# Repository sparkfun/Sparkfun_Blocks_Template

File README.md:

Edison_Mezzanine_Base
=====================

Base Board for Edison Mezzanine stack

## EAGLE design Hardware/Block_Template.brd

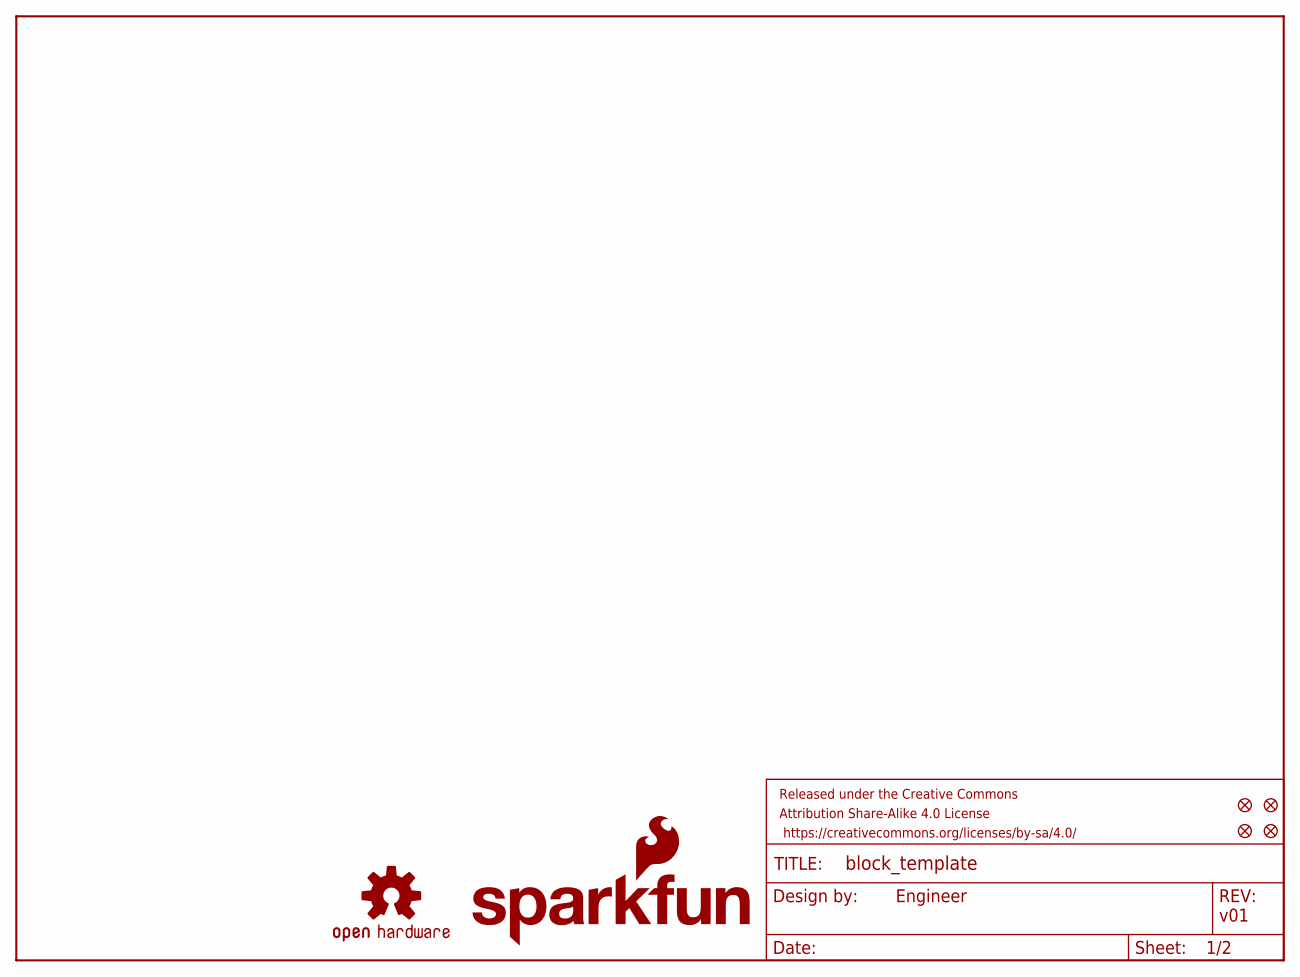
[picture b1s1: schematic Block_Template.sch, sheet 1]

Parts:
FID1, FID2, FID3, FID4: FIDUCIAL1X2; FIDUCIAL-1X2
FRAME1: FRAME-LETTER; CREATIVE_COMMONS
LOGO1: OSHW-LOGOS; OSHW-LOGO-S
LOGO4: SFE_LOGO_NAME_FLAME.1_INCH; SFE_LOGO_NAME_FLAME_.1

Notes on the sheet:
v01
Engineer

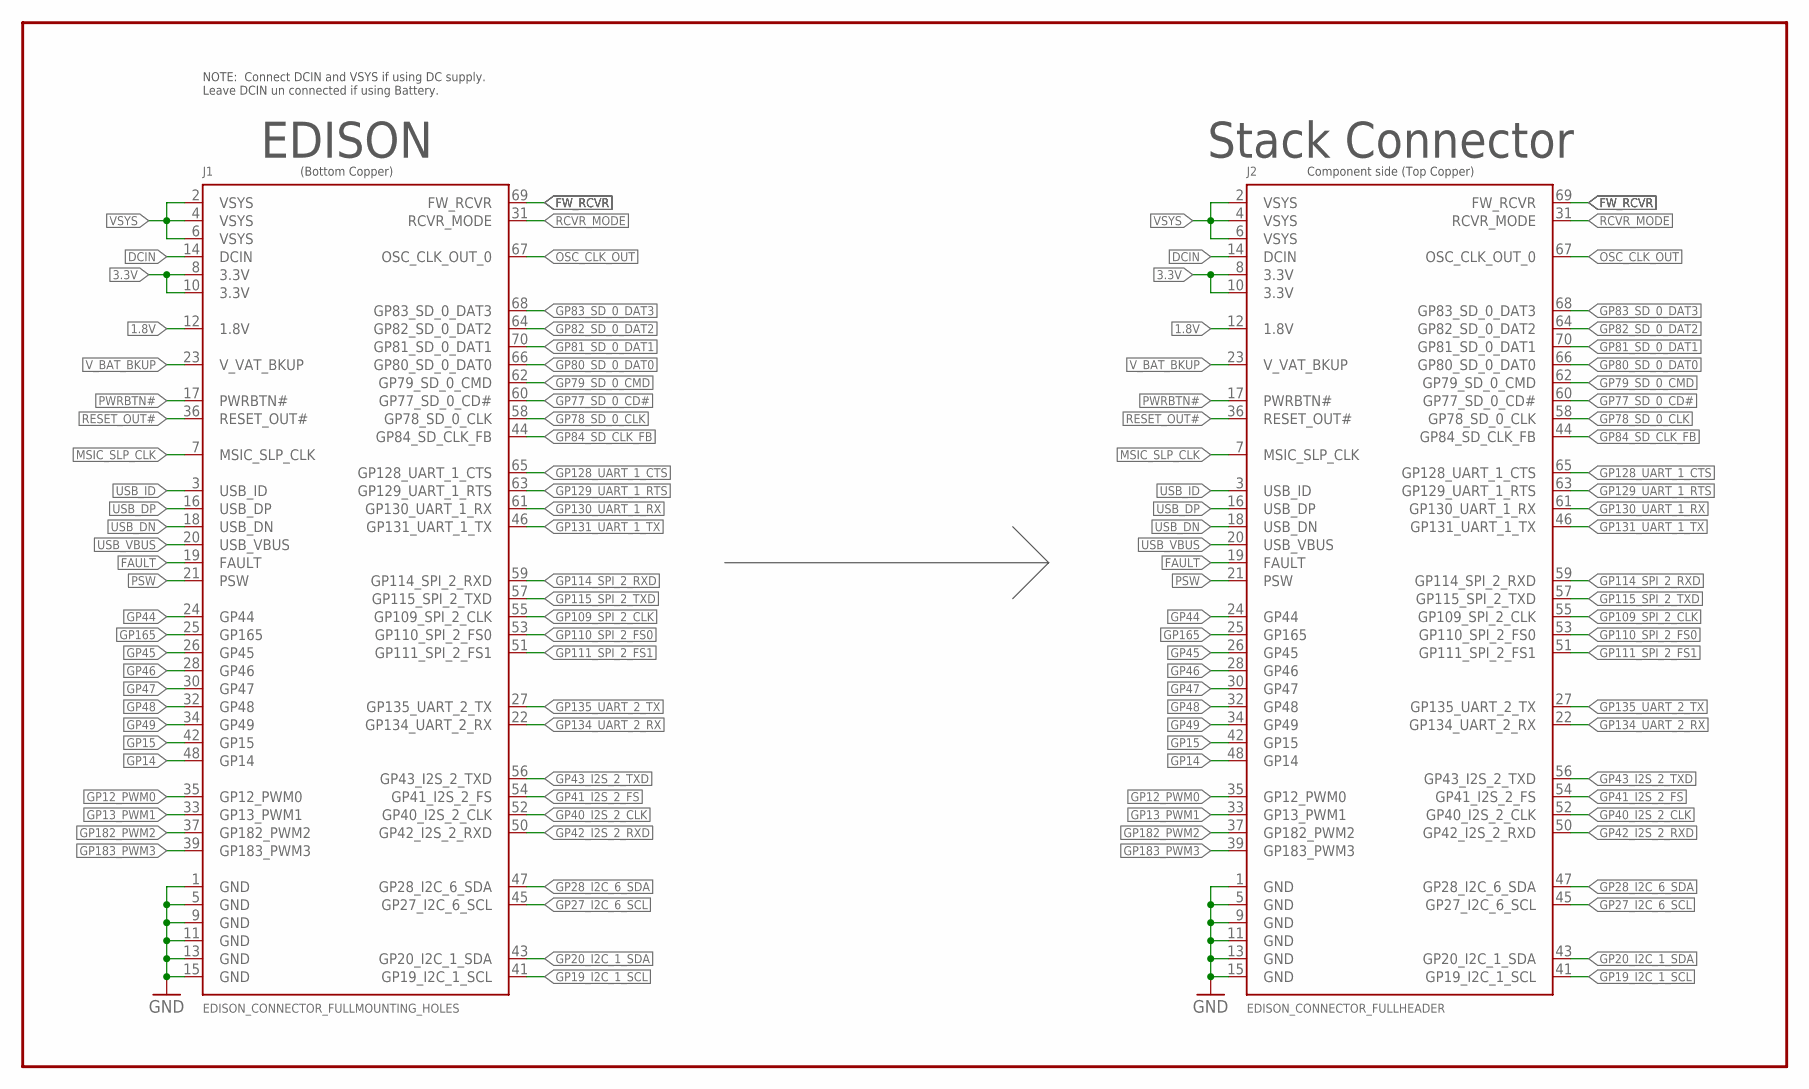
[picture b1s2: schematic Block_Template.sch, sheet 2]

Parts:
J1: EDISON_CONNECTOR_FULLMOUNTING_HOLES; EDISON_DAUGHTER
J2: EDISON_CONNECTOR_FULLHEADER; DF40C-70DP-0.4(51)

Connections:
1.8V: J1.12 (1.8V), J2.12 (1.8V)
3.3V: J1.8 (3.3V), J1.10 (3.3V), J2.8 (3.3V), J2.10 (3.3V)
DCIN: J1.14 (DCIN), J2.14 (DCIN)
FAULT: J1.19 (FAULT), J2.19 (FAULT)
FW_RCVR: J1.69 (FW_RCVR), J2.69 (FW_RCVR)
GND: J1.1 (GND), J1.5 (GND), J1.9 (GND), J1.11 (GND), J1.13 (GND), J1.15 (GND), J2.1 (GND), J2.5 (GND), J2.9 (GND), J2.11 (GND), J2.13 (GND), J2.15 (GND)
GP12_PWM0: J1.35 (GP12_PWM0), J2.35 (GP12_PWM0)
GP13_PWM1: J1.33 (GP13_PWM1), J2.33 (GP13_PWM1)
GP14: J1.48 (GP14), J2.48 (GP14)
GP15: J1.42 (GP15), J2.42 (GP15)
GP19_I2C_1_SCL: J1.41 (GP19_I2C_1_SCL), J2.41 (GP19_I2C_1_SCL)
GP20_I2C_1_SDA: J1.43 (GP20_I2C_1_SDA), J2.43 (GP20_I2C_1_SDA)
GP27_I2C_6_SCL: J1.45 (GP27_I2C_6_SCL), J2.45 (GP27_I2C_6_SCL)
GP28_I2C_6_SDA: J1.47 (GP28_I2C_6_SDA), J2.47 (GP28_I2C_6_SDA)
GP40_I2S_2_CLK: J1.52 (GP40_I2S_2_CLK), J2.52 (GP40_I2S_2_CLK)
GP41_I2S_2_FS: J1.54 (GP41_I2S_2_FS), J2.54 (GP41_I2S_2_FS)
GP42_I2S_2_RXD: J1.50 (GP42_I2S_2_RXD), J2.50 (GP42_I2S_2_RXD)
GP43_I2S_2_TXD: J1.56 (GP43_I2S_2_TXD), J2.56 (GP43_I2S_2_TXD)
GP44: J1.24 (GP44), J2.24 (GP44)
GP45: J1.26 (GP45), J2.26 (GP45)
GP46: J1.28 (GP46), J2.28 (GP46)
GP47: J1.30 (GP47), J2.30 (GP47)
GP48: J1.32 (GP48), J2.32 (GP48)
GP49: J1.34 (GP49), J2.34 (GP49)
GP77_SD_0_CD#: J1.60 (GP77_SD_0_CD#), J2.60 (GP77_SD_0_CD#)
GP78_SD_0_CLK: J1.58 (GP78_SD_0_CLK), J2.58 (GP78_SD_0_CLK)
GP79_SD_0_CMD: J1.62 (GP79_SD_0_CMD), J2.62 (GP79_SD_0_CMD)
GP80_SD_0_DAT0: J1.66 (GP80_SD_0_DAT0), J2.66 (GP80_SD_0_DAT0)
GP81_SD_0_DAT1: J1.70 (GP81_SD_0_DAT1), J2.70 (GP81_SD_0_DAT1)
GP82_SD_0_DAT2: J1.64 (GP82_SD_0_DAT2), J2.64 (GP82_SD_0_DAT2)
GP83_SD_0_DAT3: J1.68 (GP83_SD_0_DAT3), J2.68 (GP83_SD_0_DAT3)
GP84_SD_CLK_FB: J1.44 (GP84_SD_CLK_FB), J2.44 (GP84_SD_CLK_FB)
GP109_SPI_2_CLK: J1.55 (GP109_SPI_2_CLK), J2.55 (GP109_SPI_2_CLK)
GP110_SPI_2_FS0: J1.53 (GP110_SPI_2_FS0), J2.53 (GP110_SPI_2_FS0)
GP111_SPI_2_FS1: J1.51 (GP111_SPI_2_FS1), J2.51 (GP111_SPI_2_FS1)
GP114_SPI_2_RXD: J1.59 (GP114_SPI_2_RXD), J2.59 (GP114_SPI_2_RXD)
GP115_SPI_2_TXD: J1.57 (GP115_SPI_2_TXD), J2.57 (GP115_SPI_2_TXD)
GP128_UART_1_CTS: J1.65 (GP128_UART_1_CTS), J2.65 (GP128_UART_1_CTS)
GP129_UART_1_RTS: J1.63 (GP129_UART_1_RTS), J2.63 (GP129_UART_1_RTS)
GP130_UART_1_RX: J1.61 (GP130_UART_1_RX), J2.61 (GP130_UART_1_RX)
GP131_UART_1_TX: J1.46 (GP131_UART_1_TX), J2.46 (GP131_UART_1_TX)
GP134_UART_2_RX: J1.22 (GP134_UART_2_RX), J2.22 (GP134_UART_2_RX)
GP135_UART_2_TX: J1.27 (GP135_UART_2_TX), J2.27 (GP135_UART_2_TX)
GP165: J1.25 (GP165), J2.25 (GP165)
GP182_PWM2: J1.37 (GP182_PWM2), J2.37 (GP182_PWM2)
GP183_PWM3: J1.39 (GP183_PWM3), J2.39 (GP183_PWM3)
MSIC_SLP_CLK: J1.7 (MSIC_SLP_CLK), J2.7 (MSIC_SLP_CLK)
OSC_CLK_OUT: J1.67 (OSC_CLK_OUT_0), J2.67 (OSC_CLK_OUT_0)
PSW: J1.21 (PSW), J2.21 (PSW)
PWRBTN#: J1.17 (PWRBTN#), J2.17 (PWRBTN#)
RCVR_MODE: J1.31 (RCVR_MODE), J2.31 (RCVR_MODE)
RESET_OUT#: J1.36 (RESET_OUT#), J2.36 (RESET_OUT#)
USB_DN: J1.18 (USB_DN), J2.18 (USB_DN)
USB_DP: J1.16 (USB_DP), J2.16 (USB_DP)
USB_ID: J1.3 (USB_ID), J2.3 (USB_ID)
USB_VBUS: J1.20 (USB_VBUS), J2.20 (USB_VBUS)
VSYS: J1.2 (VSYS), J1.4 (VSYS), J1.6 (VSYS), J2.2 (VSYS), J2.4 (VSYS), J2.6 (VSYS)
V_BAT_BKUP: J1.23 (V_VAT_BKUP), J2.23 (V_VAT_BKUP)

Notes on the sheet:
EDISON
Stack Connector
Component side (Top Copper)
(Bottom Copper)
NOTE: Connect DCIN and VSYS if using DC supply. Leave DCIN un connected if using Battery.

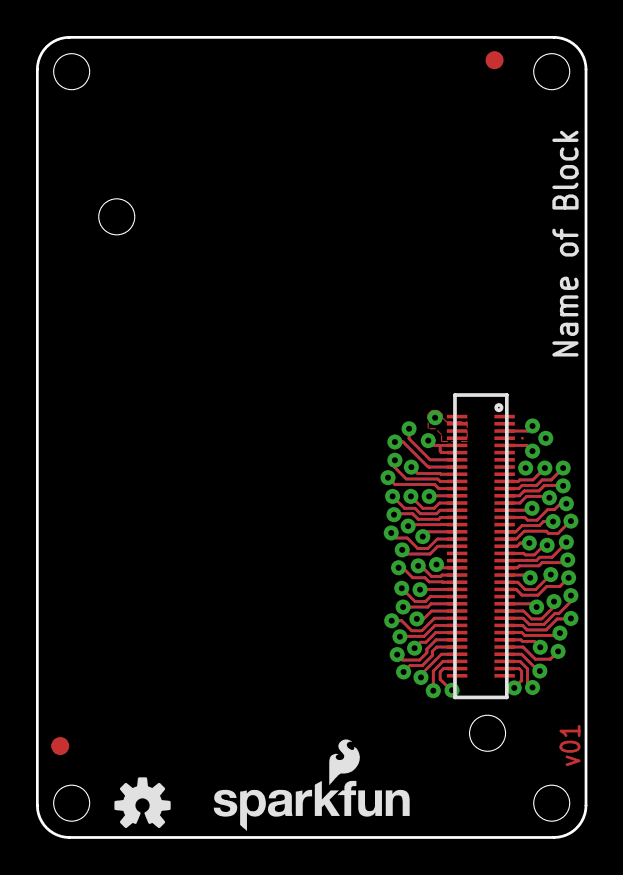
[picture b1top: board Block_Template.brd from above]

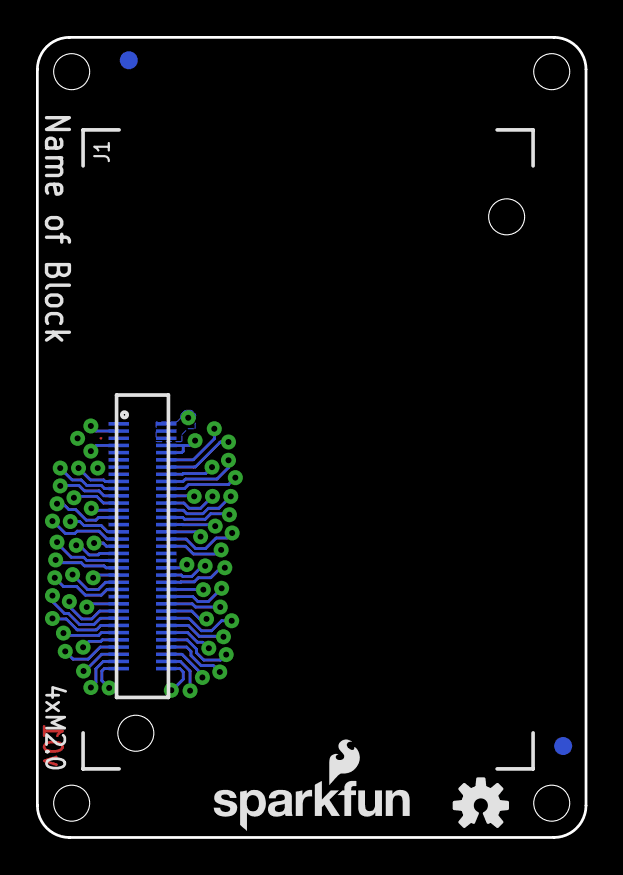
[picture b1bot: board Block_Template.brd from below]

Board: 2 copper layers, 30.5 x 44.5 mm, 11 parts (6 on the bottom side), 58 nets.

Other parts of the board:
LOGO2: OSHW-LOGOS; OSHW-LOGO-S
LOGO3: SFE_LOGO_NAME_FLAME.1_INCH; SFE_LOGO_NAME_FLAME_.1

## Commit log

2014-08-05 initial commit with new shiny template
2014-08-06 Fixed $ in names, move name from silk to tNames
2014-08-06 changed maximum board length to 2.1 to accomidate 3pin header connections.
2014-08-06 Change silk of module from borders to brackets
2014-08-06 added labels to clarify board orientation in schematic. updated library footprint for edision on demo board.
2014-08-08 added fiducials and second side logos to template
2014-08-09 - Added fiducials to both sides - flipped side name template is on - corrected 1.8v trace that was not connected. - removed my name from the designed by, Replaced with "Engineer" - Added template rev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
2014-09-11 corrected lables and removed extra packages that are no longer supported.
2014-09-11 clean-up
    Board
    - Removed duplicate CC frame
    - Adjusted sizes, ratios of text so they can be read when "Always Vector
    Font" is set
    - Adjusted positioning and alignment of text for consistency throughout
    the drawing and making the text easier to edit (expansion)
2014-09-14 replaced some changes made in pull request. updated git ignore to remover .epf
2014-09-14 removed eagle.epf
2014-09-17 modified: Hardware/Edison.lbr Corrected DCIN pin name on all schematic drawings
    modified: Hardware/Mezzanine_Template.brd
    Re-positioned Vias to accomidate extra DCIN via
    Removed connection between VSYS and DCIN for boards
    that want to use battery monitoring features
    modified: Hardware/Mezzanine_Template.sch
    Updated Schematic with current Lib Parts
2014-09-23 changed names of files
2014-09-23 corrected fill pull back
2014-09-24 Added staking pins to header
2014-09-25 cleanup
2014-10-16 corrected silk layers on connectors and added T/Brestrict to each connector to prevent bridging pours. This makes AOI easier
2014-10-17 Add tRestrict to top pad of daughter fp, turn on thermals on daughter pads
2014-10-17 Fix other connector thermals
2014-10-17 Remove spurious tPlace on daughter
2014-11-11 updated footprints to remove jumpers between connector pins. Renamed Connectors to J1 and J2. Locked vias, holes, connectors, and logos. Trying to keep things standard for future builds

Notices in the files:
parts and their libraries:
SparkFun-Aesthetics: Licensing: Creative Commons ShareAlike 4.0 International - https://creativecommons.org/licenses/by-sa/4.0
SparkFun-Aesthetics: Released under the Creative Commons Attribution Share-Alike 4.0 License
SparkFun-Aesthetics: https://creativecommons.org/licenses/by-sa/4.0
